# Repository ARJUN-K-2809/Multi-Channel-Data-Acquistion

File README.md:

# ⚡ 8-Channel High-Speed MultiChannel DAQ System (500kSPS)

## 📖 Overview

This project focuses on the development of a **high-speed, multi-channel data acquisition system (DAQ)** capable of sampling **8 differential input channels** at an aggregate rate of **500kSPS**.  

The system is designed for use in **high-speed sensor data acquisition**, **industrial monitoring**, **control systems**, and **real-time signal analysis** where accuracy, low-noise design, and scalability are critical.

This DAQ emphasizes:
- Differential signal integrity  
- Noise immunity  
- Modular expandability  
- Real-time digital data streaming  

---

## 🚀 Key Features

- ✅ **8 Differential Analog Input Channels**  
- ✅ **500kSPS High-Speed ADC System**  
- ✅ Precision Differential Signal Conditioning Front-End  
- ✅ Optimized low-noise PCB layout with analog/digital isolation  
- ✅ SPI Communication Interface for MCU/FPGA systems  
- ✅ Onboard test points for debugging and signal probing  
- ✅ Designed for integration with embedded platforms  
- ✅ Expandable architecture for future scaling  

---

## ⚙️ System Architecture

The system is split into four main functional blocks:

1. **Differential Analog Front-End**  
   - Converts sensor signals into stable, low-noise differential outputs  
   - Protects ADC inputs from overvoltage and noise  

2. **8-Channel High-Speed ADC**  
   - Supports high-precision sampling  
   - Total throughput up to **500,000 samples per second**  
   - Compatible with SPI-based microcontrollers or FPGA systems  

3. **Power Management**  
   - Low-noise LDO regulators for analog and digital supplies  
   - Filtered power domains for improved performance  

4. **Digital Interface Layer**  
   - Standard SPI interface  
   - Optional external clock input  
   - Compatible with STM32, ESP32, and FPGA boards  

---

## 📊 Current Project Status

✅ PCB Designed  
✅ PCB Fabricated  
✅ Components Assembled  
🧪 **Hardware Testing In Progress**  
🧪 Signal Integrity Verification  
🧪 ADC Performance Characterization  
🧪 Noise and Crosstalk Measurements  

The board is currently being tested to validate:
- Sampling stability at 500kSPS  
- Channel-to-channel isolation  
- Differential signal performance  
- Noise floor and dynamic range  

---

## 🖥️ Hardware Specifications

| Feature | Specification |
|--------|--------------|
| Input Channels | 8 Differential |
| Max Sampling Rate | 500kSPS |
| Resolution | Configurable (depends on ADC used) |
| Communication | SPI |
| PCB Layers | 2-Layer |
| Front-End Type | Fully Differential |

---

## 🧪 Testing and Validation

Ongoing hardware testing includes:

- ✔ ADC linearity and INL/DNL testing  
- ✔ High-frequency signal response  
- ✔ Noise spectrum analysis  
- ✔ Crosstalk measurement across channels  
- ✔ Long-term stability analysis  

Preliminary results indicate **stable sampling performance close to the target 500kSPS rate**.

Detailed test results will be added soon in the `/docs` folder.

---

## 🔌 Planned Firmware Features

Firmware development will support:

- Interrupt or DMA-based ADC sampling  
- 8-channel data multiplexing and control  
- Circular buffering for real-time streaming  
- Dynamic sampling configuration  
- USB/UART data streaming to PC  
- Simple command-based interface  

Supported platforms:
- FPGA-based controllers  

---

## 🎯 Applications

This DAQ system is ideal for:

- Vibration analysis  
- Industrial automation  
- Biomedical instrumentation (non-invasive)  
- Lab measurement equipment  
- Embedded data logging  
- Multi-sensor arrays  

---

## 🔮 Future Improvements

- Higher channel count version (16/32 channels)  
- Higher sampling rate variants  
- USB-C interface  
- FPGA-based acquisition engine  
- Onboard signal processing  
- Isolation for industrial use  

---

## 🤝 Contributions & Collaboration

Contributions and testing support are welcome!  
If you’re interested in collaborating on firmware, software, or hardware validation — feel free to open an issue or fork this repository.

---

## 📜 License

This project is released under the **MIT License**.  
You are free to modify, reuse, and distribute with proper credit.

---

## ⭐ Support

If you find this project useful, feel free to star ⭐ this repo and share feedback!

## 📦 Repository Structure

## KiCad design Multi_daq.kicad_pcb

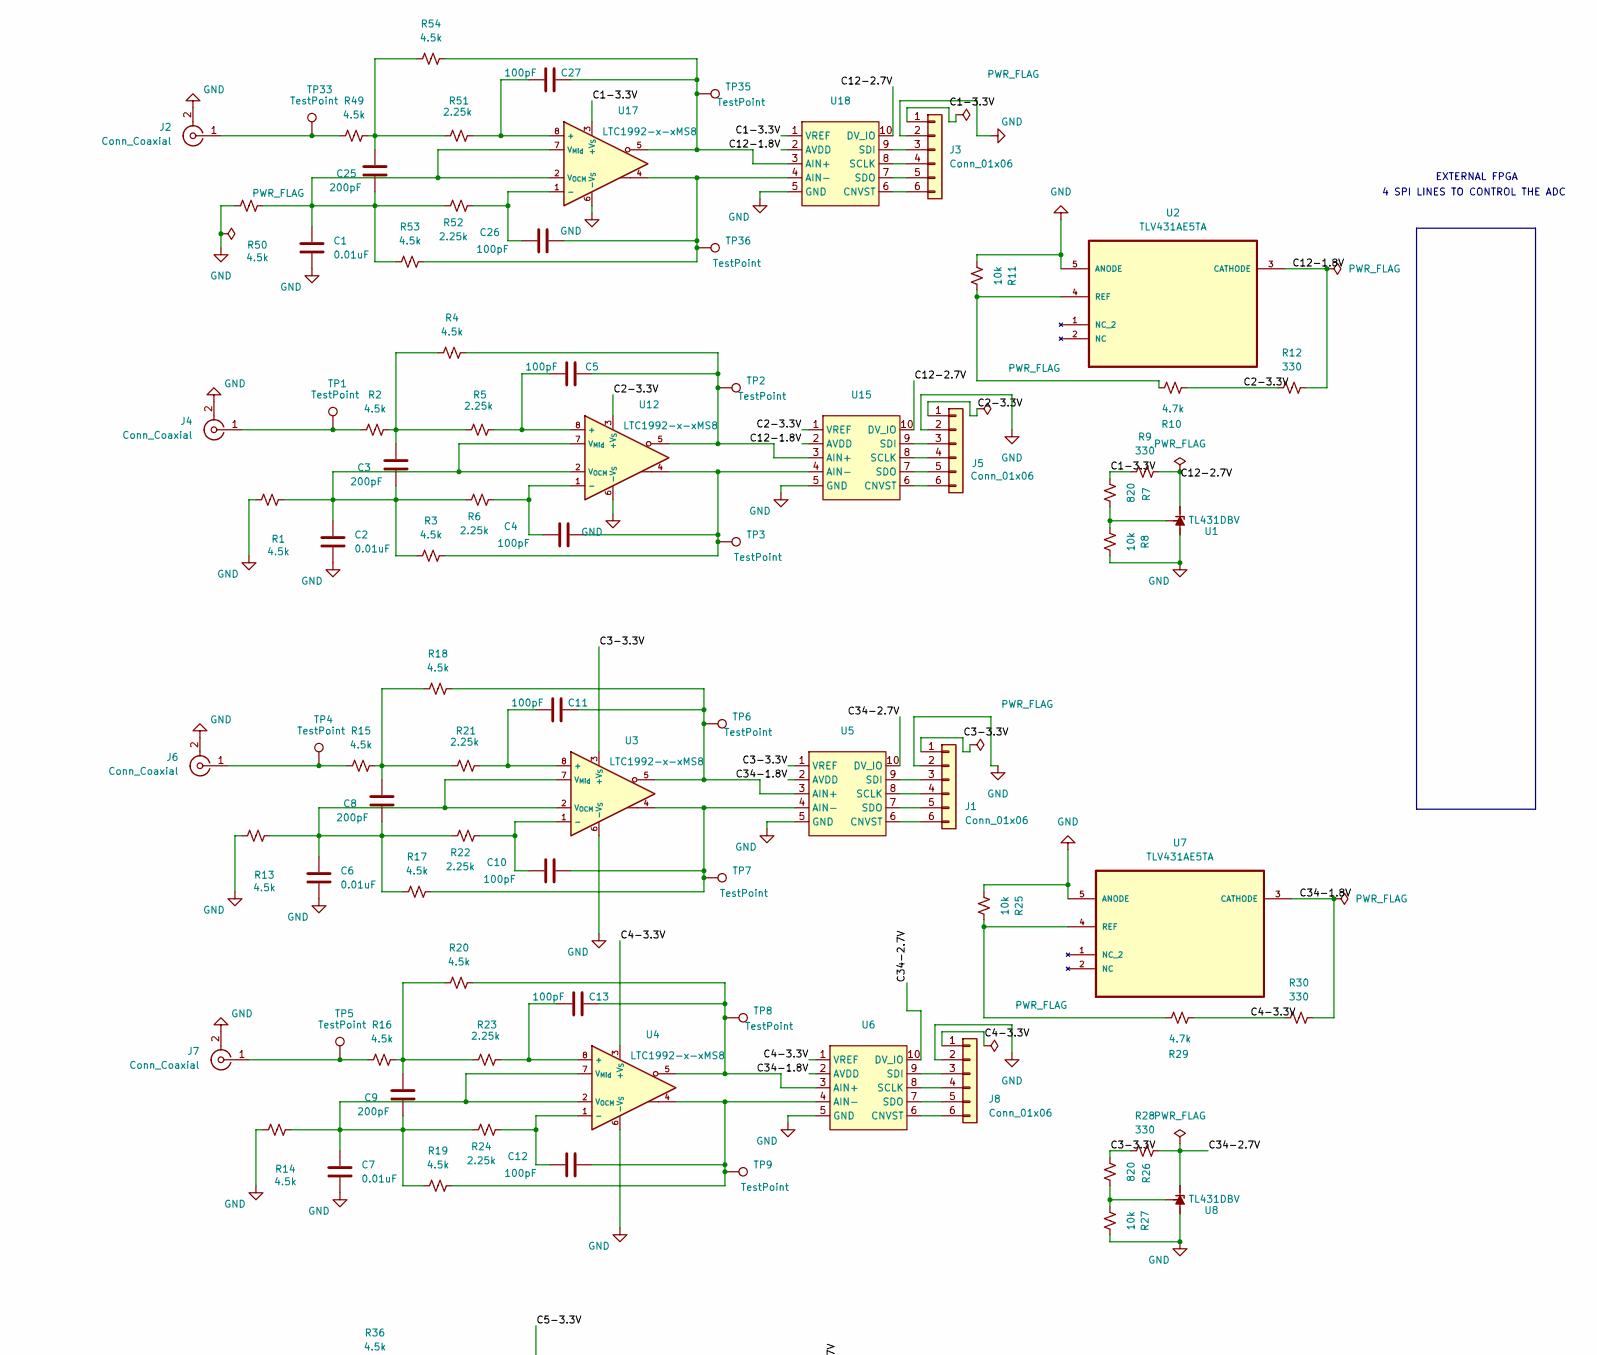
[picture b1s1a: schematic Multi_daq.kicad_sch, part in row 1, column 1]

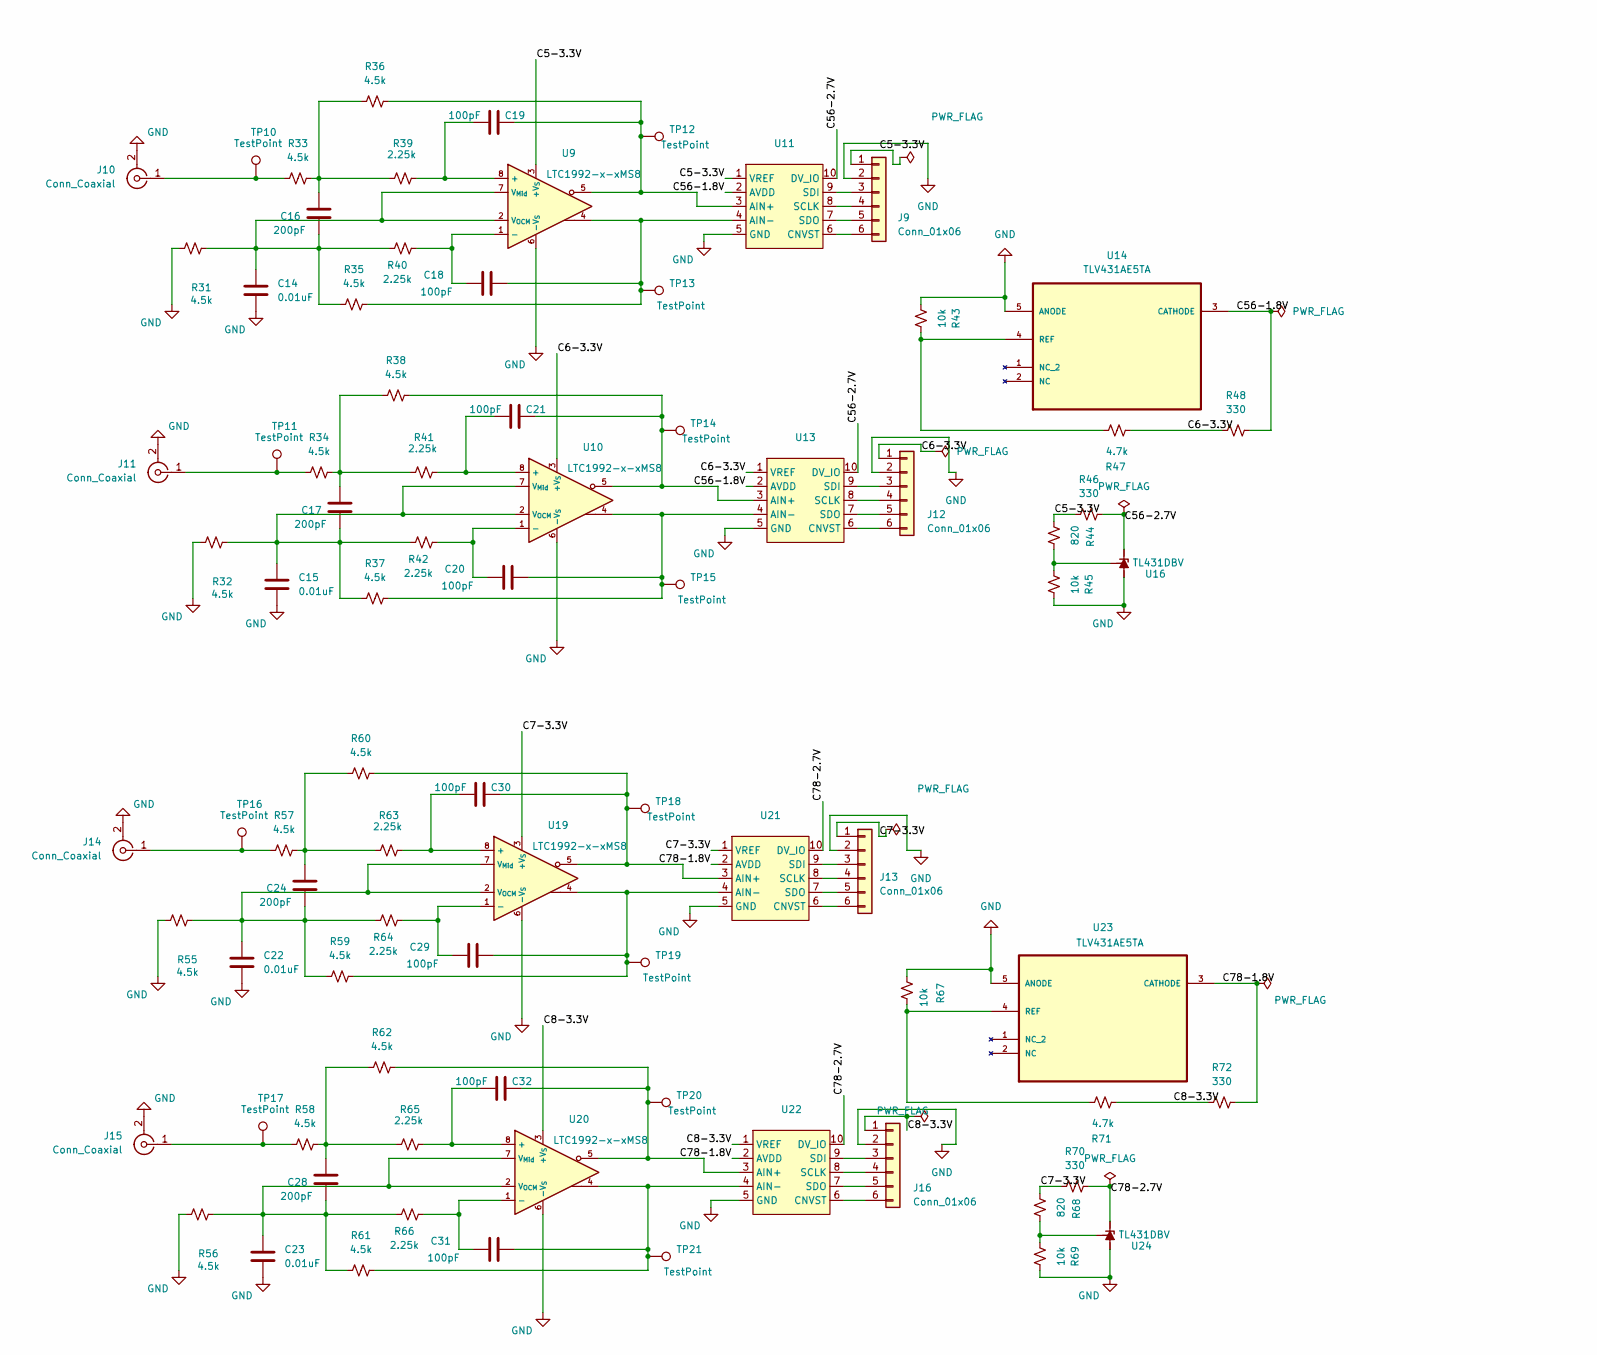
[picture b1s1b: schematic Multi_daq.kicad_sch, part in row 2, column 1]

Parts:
C1, C2, C6, C7, C14, C15, C22, C23: 0.01uF; C_Disc_D5.0mm_W2.5mm_P2.50mm
C3, C8, C9, C16, C17, C24, C25, C28: 200pF; C_Disc_D5.0mm_W2.5mm_P2.50mm
C4, C5, C10, C11, C12, C13, C18, C19, C20, C21, C26, C27, C29, C30, C31, C32: 100pF; C_Disc_D5.0mm_W2.5mm_P2.50mm
J1, J3, J5, J8, J9, J12, J13, J16: Conn_01x06; PinHeader_1x06_P2.54mm_Vertical
J2, J4, J6, J7, J10, J11, J14, J15: Conn_Coaxial; BNC-modified
R1, R2, R3, R4, R13, R14, R15, R16, R17, R18, R19, R20, R31, R32, R33, R34, R35, R36, R37, R38, R49, R50, R53, R54, R55, R56, R57, R58, R59, R60, R61, R62: 4.5k; R_Axial_DIN0207_L6.3mm_D2.5mm_P7.62mm_Horizontal
R5, R6, R21, R22, R23, R24, R39, R40, R41, R42, R51, R52, R63, R64, R65, R66: 2.25k; R_Axial_DIN0207_L6.3mm_D2.5mm_P7.62mm_Horizontal
R7, R26, R44, R68: 820; R_Axial_DIN0207_L6.3mm_D2.5mm_P7.62mm_Horizontal
R8, R11, R25, R27, R43, R45, R67, R69: 10k; R_Axial_DIN0207_L6.3mm_D2.5mm_P7.62mm_Horizontal
R9, R12, R28, R30, R46, R48, R70, R72: 330; R_Axial_DIN0207_L6.3mm_D2.5mm_P7.62mm_Horizontal
R10, R29, R47, R71: 4.7k; R_Axial_DIN0207_L6.3mm_D2.5mm_P7.62mm_Horizontal
TP1, TP2, TP3, TP4, TP5, TP6, TP7, TP8, TP9, TP10, TP11, TP12, TP13, TP14, TP15, TP16, TP17, TP18, TP19, TP20, TP21, TP33, TP35, TP36: TestPoint; TestPoint_Loop_D2.50mm_Drill1.0mm
U1, U8, U16, U24: TL431DBV; SOT-23-5
U2, U7, U14, U23: TLV431AE5TA; MPN TLV431AE5TA
U3, U4, U9, U10, U12, U17, U19, U20: LTC1992-x-xMS8; MSOP-8_3x3mm_P0.65mm
U5, U6, U11, U13, U15, U18, U21, U22: SOP50P490X110-10N

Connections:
/C1-3.3V: J3.1, R7.1, R9.1, U17.3 (+V_{S}), U18.1 (VREF)
/C2-3.3V: J5.1, R10.1, R12.1, U12.3 (+V_{S}), U15.1 (VREF)
/C3-3.3V: J1.1, R26.1, R28.1, U3.3 (+V_{S}), U5.1 (VREF)
/C4-3.3V: J8.1, R29.1, R30.1, U4.3 (+V_{S}), U6.1 (VREF)
/C5-3.3V: J9.1, R44.1, R46.1, U9.3 (+V_{S}), U11.1 (VREF)
/C6-3.3V: J12.1, R47.1, R48.1, U10.3 (+V_{S}), U13.1 (VREF)
/C7-3.3V: J13.1, R68.1, R70.1, U19.3 (+V_{S}), U21.1 (VREF)
/C8-3.3V: J16.1, R71.1, R72.1, U20.3 (+V_{S}), U22.1 (VREF)
/C12-1.8V: R12.2, U2.3 (CATHODE), U15.2 (AVDD), U18.2 (AVDD)
/C12-2.7V: R9.2, U1.3 (K), U15.10 (DV_IO), U18.10 (DV_IO)
/C34-1.8V: R30.2, U5.2 (AVDD), U6.2 (AVDD), U7.3 (CATHODE)
/C34-2.7V: R28.2, U5.10 (DV_IO), U6.10 (DV_IO), U8.3 (K)
/C56-1.8V: R48.2, U11.2 (AVDD), U13.2 (AVDD), U14.3 (CATHODE)
/C56-2.7V: R46.2, U11.10 (DV_IO), U13.10 (DV_IO), U16.3 (K)
/C78-1.8V: R72.2, U21.2 (AVDD), U22.2 (AVDD), U23.3 (CATHODE)
/C78-2.7V: R70.2, U21.10 (DV_IO), U22.10 (DV_IO), U24.3 (K)
GND: C1.2, C2.2, C6.2, C7.2, C14.2, C15.2, C22.2, C23.2, J1.2, J2.2 (Ext), J3.2, J4.2 (Ext), J5.2, J6.2 (Ext), J7.2 (Ext), J8.2, J9.2, J10.2 (Ext), J11.2 (Ext), J12.2, J13.2, J14.2 (Ext), J15.2 (Ext), J16.2, R1.1, R8.1, R11.2, R13.1, R14.1, R25.2, R27.1, R31.1, R32.1, R43.2, R45.1, R50.1, R55.1, R56.1, R67.2, R69.1, U1.5 (A), U2.5 (ANODE), U3.6 (-V_{S}), U4.6 (-V_{S}), U5.5 (GND), U6.5 (GND), U7.5 (ANODE), U8.5 (A), U9.6 (-V_{S}), U10.6 (-V_{S}), U11.5 (GND), U12.6 (-V_{S}), U13.5 (GND), U14.5 (ANODE), U15.5 (GND), U16.5 (A), U17.6 (-V_{S}), U18.5 (GND), U19.6 (-V_{S}), U20.6 (-V_{S}), U21.5 (GND), U22.5 (GND), U23.5 (ANODE), U24.5 (A)
unnamed: C3.2, R2.2, R4.1, R5.1
unnamed: C8.2, R15.2, R18.1, R21.1
unnamed: C9.2, R16.2, R20.1, R23.1
unnamed: C16.2, R33.2, R36.1, R39.1
unnamed: C17.2, R34.2, R38.1, R41.1
unnamed: C24.2, R57.2, R60.1, R63.1
unnamed: C25.2, R49.2, R51.1, R54.1
unnamed: C28.2, R58.2, R62.1, R65.1
unnamed: J1.3, U5.9 (SDI)
unnamed: J1.4, U5.8 (SCLK)
unnamed: J1.5, U5.7 (SDO)
unnamed: J1.6, U5.6 (CNVST)
unnamed: J2.1 (In), R49.1, TP33.1
unnamed: J3.3, U18.9 (SDI)
unnamed: J3.4, U18.8 (SCLK)
unnamed: J3.5, U18.7 (SDO)
unnamed: J3.6, U18.6 (CNVST)
unnamed: J4.1 (In), R2.1, TP1.1
unnamed: J5.3, U15.9 (SDI)
unnamed: J5.4, U15.8 (SCLK)
unnamed: J5.5, U15.7 (SDO)
unnamed: J5.6, U15.6 (CNVST)
unnamed: J6.1 (In), R15.1, TP4.1
unnamed: J7.1 (In), R16.1, TP5.1
unnamed: J8.3, U6.9 (SDI)
unnamed: J8.4, U6.8 (SCLK)
unnamed: J8.5, U6.7 (SDO)
unnamed: J8.6, U6.6 (CNVST)
unnamed: J9.3, U11.9 (SDI)
unnamed: J9.4, U11.8 (SCLK)
unnamed: J9.5, U11.7 (SDO)
unnamed: J9.6, U11.6 (CNVST)
unnamed: J10.1 (In), R33.1, TP10.1
unnamed: J11.1 (In), R34.1, TP11.1
unnamed: J12.3, U13.9 (SDI)
unnamed: J12.4, U13.8 (SCLK)
unnamed: J12.5, U13.7 (SDO)
unnamed: J12.6, U13.6 (CNVST)
unnamed: J13.3, U21.9 (SDI)
unnamed: J13.4, U21.8 (SCLK)
unnamed: J13.5, U21.7 (SDO)
unnamed: J13.6, U21.6 (CNVST)
unnamed: J14.1 (In), R57.1, TP16.1
unnamed: J15.1 (In), R58.1, TP17.1
unnamed: J16.3, U22.9 (SDI)
unnamed: J16.4, U22.8 (SCLK)
unnamed: J16.5, U22.7 (SDO)
unnamed: J16.6, U22.6 (CNVST)
unnamed: R7.2, R8.2, U1.4 (REF)
unnamed: R10.2, R11.1, U2.4 (REF)
unnamed: C11.1, R21.2, U3.8 (+)
unnamed: C10.1, R22.2, U3.1 (-)
unnamed: C6.1, C8.1, R13.2, R17.1, R22.1, U3.2 (V_{OCM}), U3.7 (V_{Mid})
unnamed: C13.1, R23.2, U4.8 (+)
unnamed: C12.1, R24.2, U4.1 (-)
unnamed: C7.1, C9.1, R14.2, R19.1, R24.1, U4.2 (V_{OCM}), U4.7 (V_{Mid})
unnamed: C11.2, R18.2, TP6.1, U3.5, U5.3 (AIN+)
unnamed: C10.2, R17.2, TP7.1, U3.4, U5.4 (AIN-)
unnamed: C13.2, R20.2, TP8.1, U4.5, U6.3 (AIN+)
unnamed: C12.2, R19.2, TP9.1, U4.4, U6.4 (AIN-)
unnamed: R25.1, R29.2, U7.4 (REF)
unnamed: R26.2, R27.2, U8.4 (REF)
unnamed: C19.1, R39.2, U9.8 (+)
unnamed: C18.1, R40.2, U9.1 (-)
unnamed: C14.1, C16.1, R31.2, R35.1, R40.1, U9.2 (V_{OCM}), U9.7 (V_{Mid})
unnamed: C21.1, R41.2, U10.8 (+)
unnamed: C20.1, R42.2, U10.1 (-)
unnamed: C15.1, C17.1, R32.2, R37.1, R42.1, U10.2 (V_{OCM}), U10.7 (V_{Mid})
unnamed: C19.2, R36.2, TP12.1, U9.5, U11.3 (AIN+)
unnamed: C18.2, R35.2, TP13.1, U9.4, U11.4 (AIN-)
unnamed: C5.1, R5.2, U12.8 (+)
unnamed: C4.1, R6.2, U12.1 (-)
unnamed: C2.1, C3.1, R1.2, R3.1, R6.1, U12.2 (V_{OCM}), U12.7 (V_{Mid})
unnamed: C21.2, R38.2, TP14.1, U10.5, U13.3 (AIN+)
unnamed: C20.2, R37.2, TP15.1, U10.4, U13.4 (AIN-)
unnamed: R43.1, R47.2, U14.4 (REF)
unnamed: C5.2, R4.2, TP2.1, U12.5, U15.3 (AIN+)
unnamed: C4.2, R3.2, TP3.1, U12.4, U15.4 (AIN-)
unnamed: R44.2, R45.2, U16.4 (REF)
unnamed: C27.1, R51.2, U17.8 (+)
unnamed: C26.1, R52.2, U17.1 (-)
unnamed: C1.1, C25.1, R50.2, R52.1, R53.1, U17.2 (V_{OCM}), U17.7 (V_{Mid})
unnamed: C27.2, R54.2, TP35.1, U17.5, U18.3 (AIN+)
unnamed: C26.2, R53.2, TP36.1, U17.4, U18.4 (AIN-)
unnamed: C30.1, R63.2, U19.8 (+)
unnamed: C29.1, R64.2, U19.1 (-)
unnamed: C22.1, C24.1, R55.2, R59.1, R64.1, U19.2 (V_{OCM}), U19.7 (V_{Mid})
unnamed: C32.1, R65.2, U20.8 (+)
unnamed: C31.1, R66.2, U20.1 (-)
unnamed: C23.1, C28.1, R56.2, R61.1, R66.1, U20.2 (V_{OCM}), U20.7 (V_{Mid})
unnamed: C30.2, R60.2, TP18.1, U19.5, U21.3 (AIN+)
unnamed: C29.2, R59.2, TP19.1, U19.4, U21.4 (AIN-)
unnamed: C32.2, R62.2, TP20.1, U20.5, U22.3 (AIN+)
unnamed: C31.2, R61.2, TP21.1, U20.4, U22.4 (AIN-)
unnamed: R67.1, R71.2, U23.4 (REF)
unnamed: R68.2, R69.2, U24.4 (REF)

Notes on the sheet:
EXTERNAL FPGA
4 SPI LINES TO CONTROL THE ADC

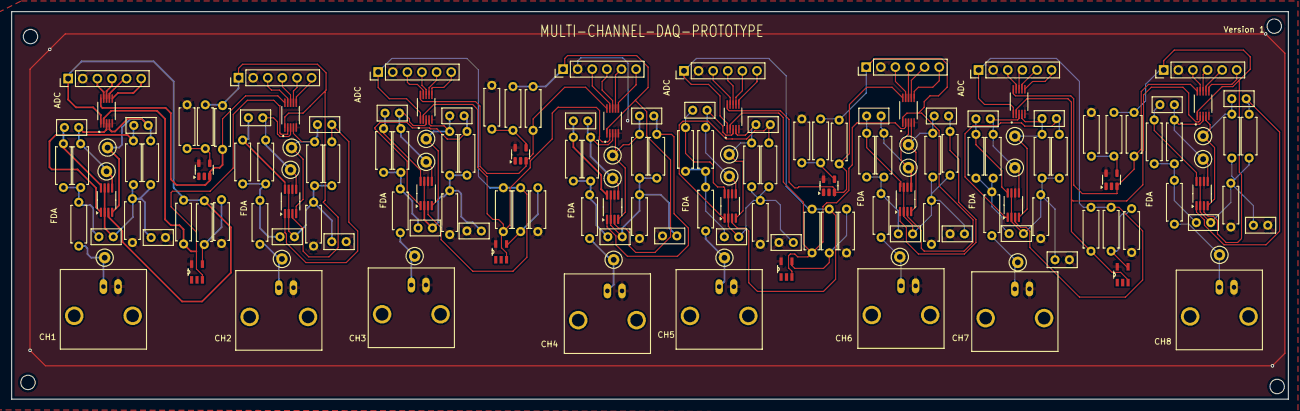
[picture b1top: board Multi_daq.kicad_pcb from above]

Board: 2 copper layers, 222.0 x 67.4 mm, 168 parts (0 on the bottom side), 113 nets.

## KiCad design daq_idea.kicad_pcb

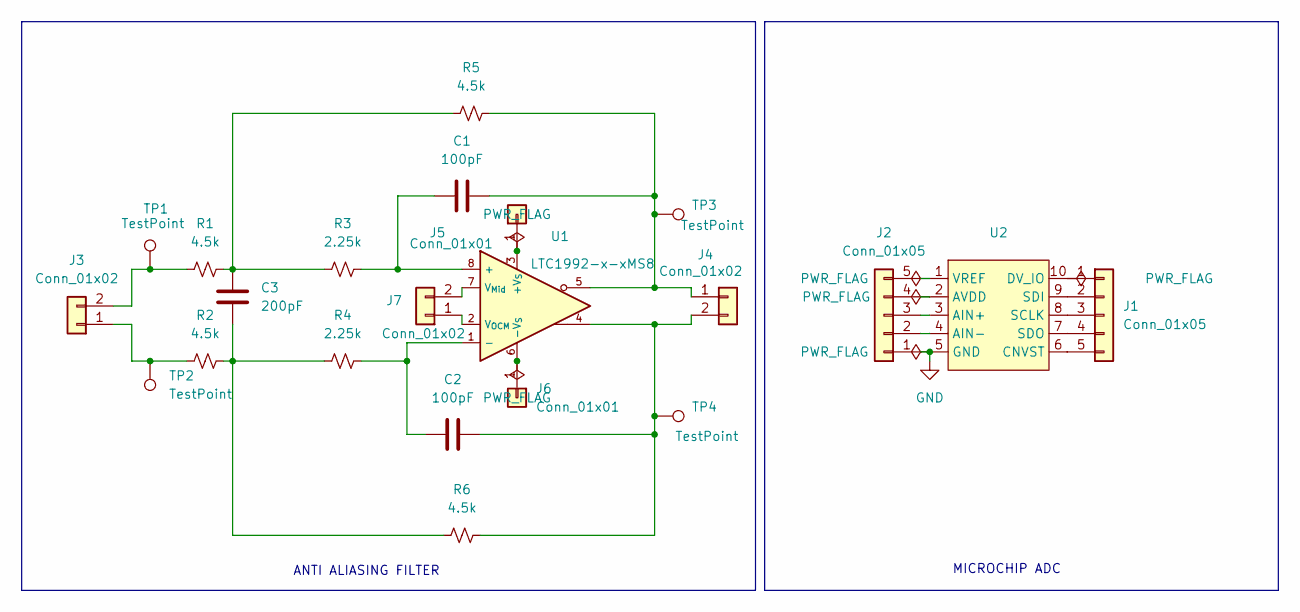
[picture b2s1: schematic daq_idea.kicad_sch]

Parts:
C1, C2: 100pF; C_Disc_D5.0mm_W2.5mm_P2.50mm
C3: 200pF; C_Disc_D5.0mm_W2.5mm_P2.50mm
J1, J2: Conn_01x05; PinHeader_1x05_P2.54mm_Vertical
J3, J4, J7: Conn_01x02; PinHeader_1x02_P2.54mm_Vertical
J5, J6: Conn_01x01; PinHeader_1x01_P1.00mm_Vertical
R1, R2, R5, R6: 4.5k; R_Axial_DIN0207_L6.3mm_D2.5mm_P7.62mm_Horizontal
R3, R4: 2.25k; R_Axial_DIN0207_L6.3mm_D2.5mm_P7.62mm_Horizontal
TP1, TP2, TP3, TP4: TestPoint; TestPoint_Loop_D2.50mm_Drill1.0mm
U1: LTC1992-x-xMS8; MSOP-8_3x3mm_P0.65mm
U2: SOP50P490X110-10N

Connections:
GND: J2.1, U2.5 (GND)
unnamed: C3.1, R2.2, R4.1, R6.1
unnamed: C3.2, R1.2, R3.1, R5.1
unnamed: J1.1, U2.10 (DV_IO)
unnamed: J1.2, U2.9 (SDI)
unnamed: J1.3, U2.8 (SCLK)
unnamed: J1.4, U2.7 (SDO)
unnamed: J1.5, U2.6 (CNVST)
unnamed: J2.2, U2.4 (AIN-)
unnamed: J2.3, U2.3 (AIN+)
unnamed: J2.4, U2.2 (AVDD)
unnamed: J2.5, U2.1 (VREF)
unnamed: J3.1, R2.1, TP2.1
unnamed: J3.2, R1.1, TP1.1
unnamed: C1.2, J4.1, R5.2, TP3.1, U1.5
unnamed: C2.2, J4.2, R6.2, TP4.1, U1.4
unnamed: J5.1, U1.3 (+V_{S})
unnamed: J6.1, U1.6 (-V_{S})
unnamed: J7.1, U1.2 (V_{OCM})
unnamed: J7.2, U1.7 (V_{Mid})
unnamed: C1.1, R3.2, U1.8 (+)
unnamed: C2.1, R4.2, U1.1 (-)

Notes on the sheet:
ANTI ALIASING FILTER
MICROCHIP ADC

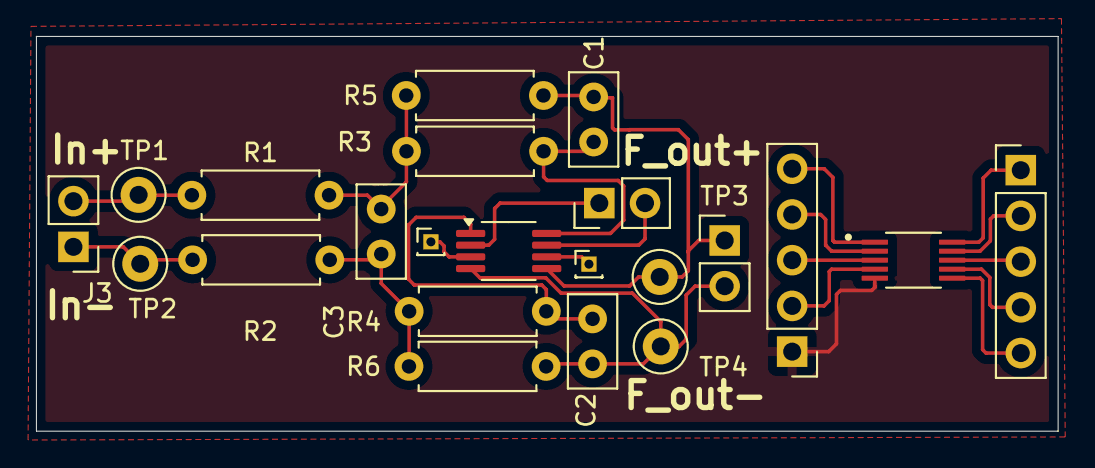
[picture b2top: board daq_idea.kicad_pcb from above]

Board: 2 copper layers, 56.8 x 21.9 mm, 22 parts (0 on the bottom side), 22 nets.

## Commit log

2025-11-23 Mutli_Channel_PCB_update
2025-11-23 Revise README for 8-Channel High-Speed DAQ System
    Updated README to reflect changes in project focus and features, including an emphasis on an 8-channel, 500kSPS data acquisition system. Enhanced sections on system architecture, key features, and fu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
